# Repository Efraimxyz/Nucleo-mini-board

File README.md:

# Nucleo-mini-board
This is the design of a pcb that integrates the STM Nucleo-board along with external power capabilities.
The pcb itself has push buttons, LEDs, an OLED screen and an integrated acceleromter.

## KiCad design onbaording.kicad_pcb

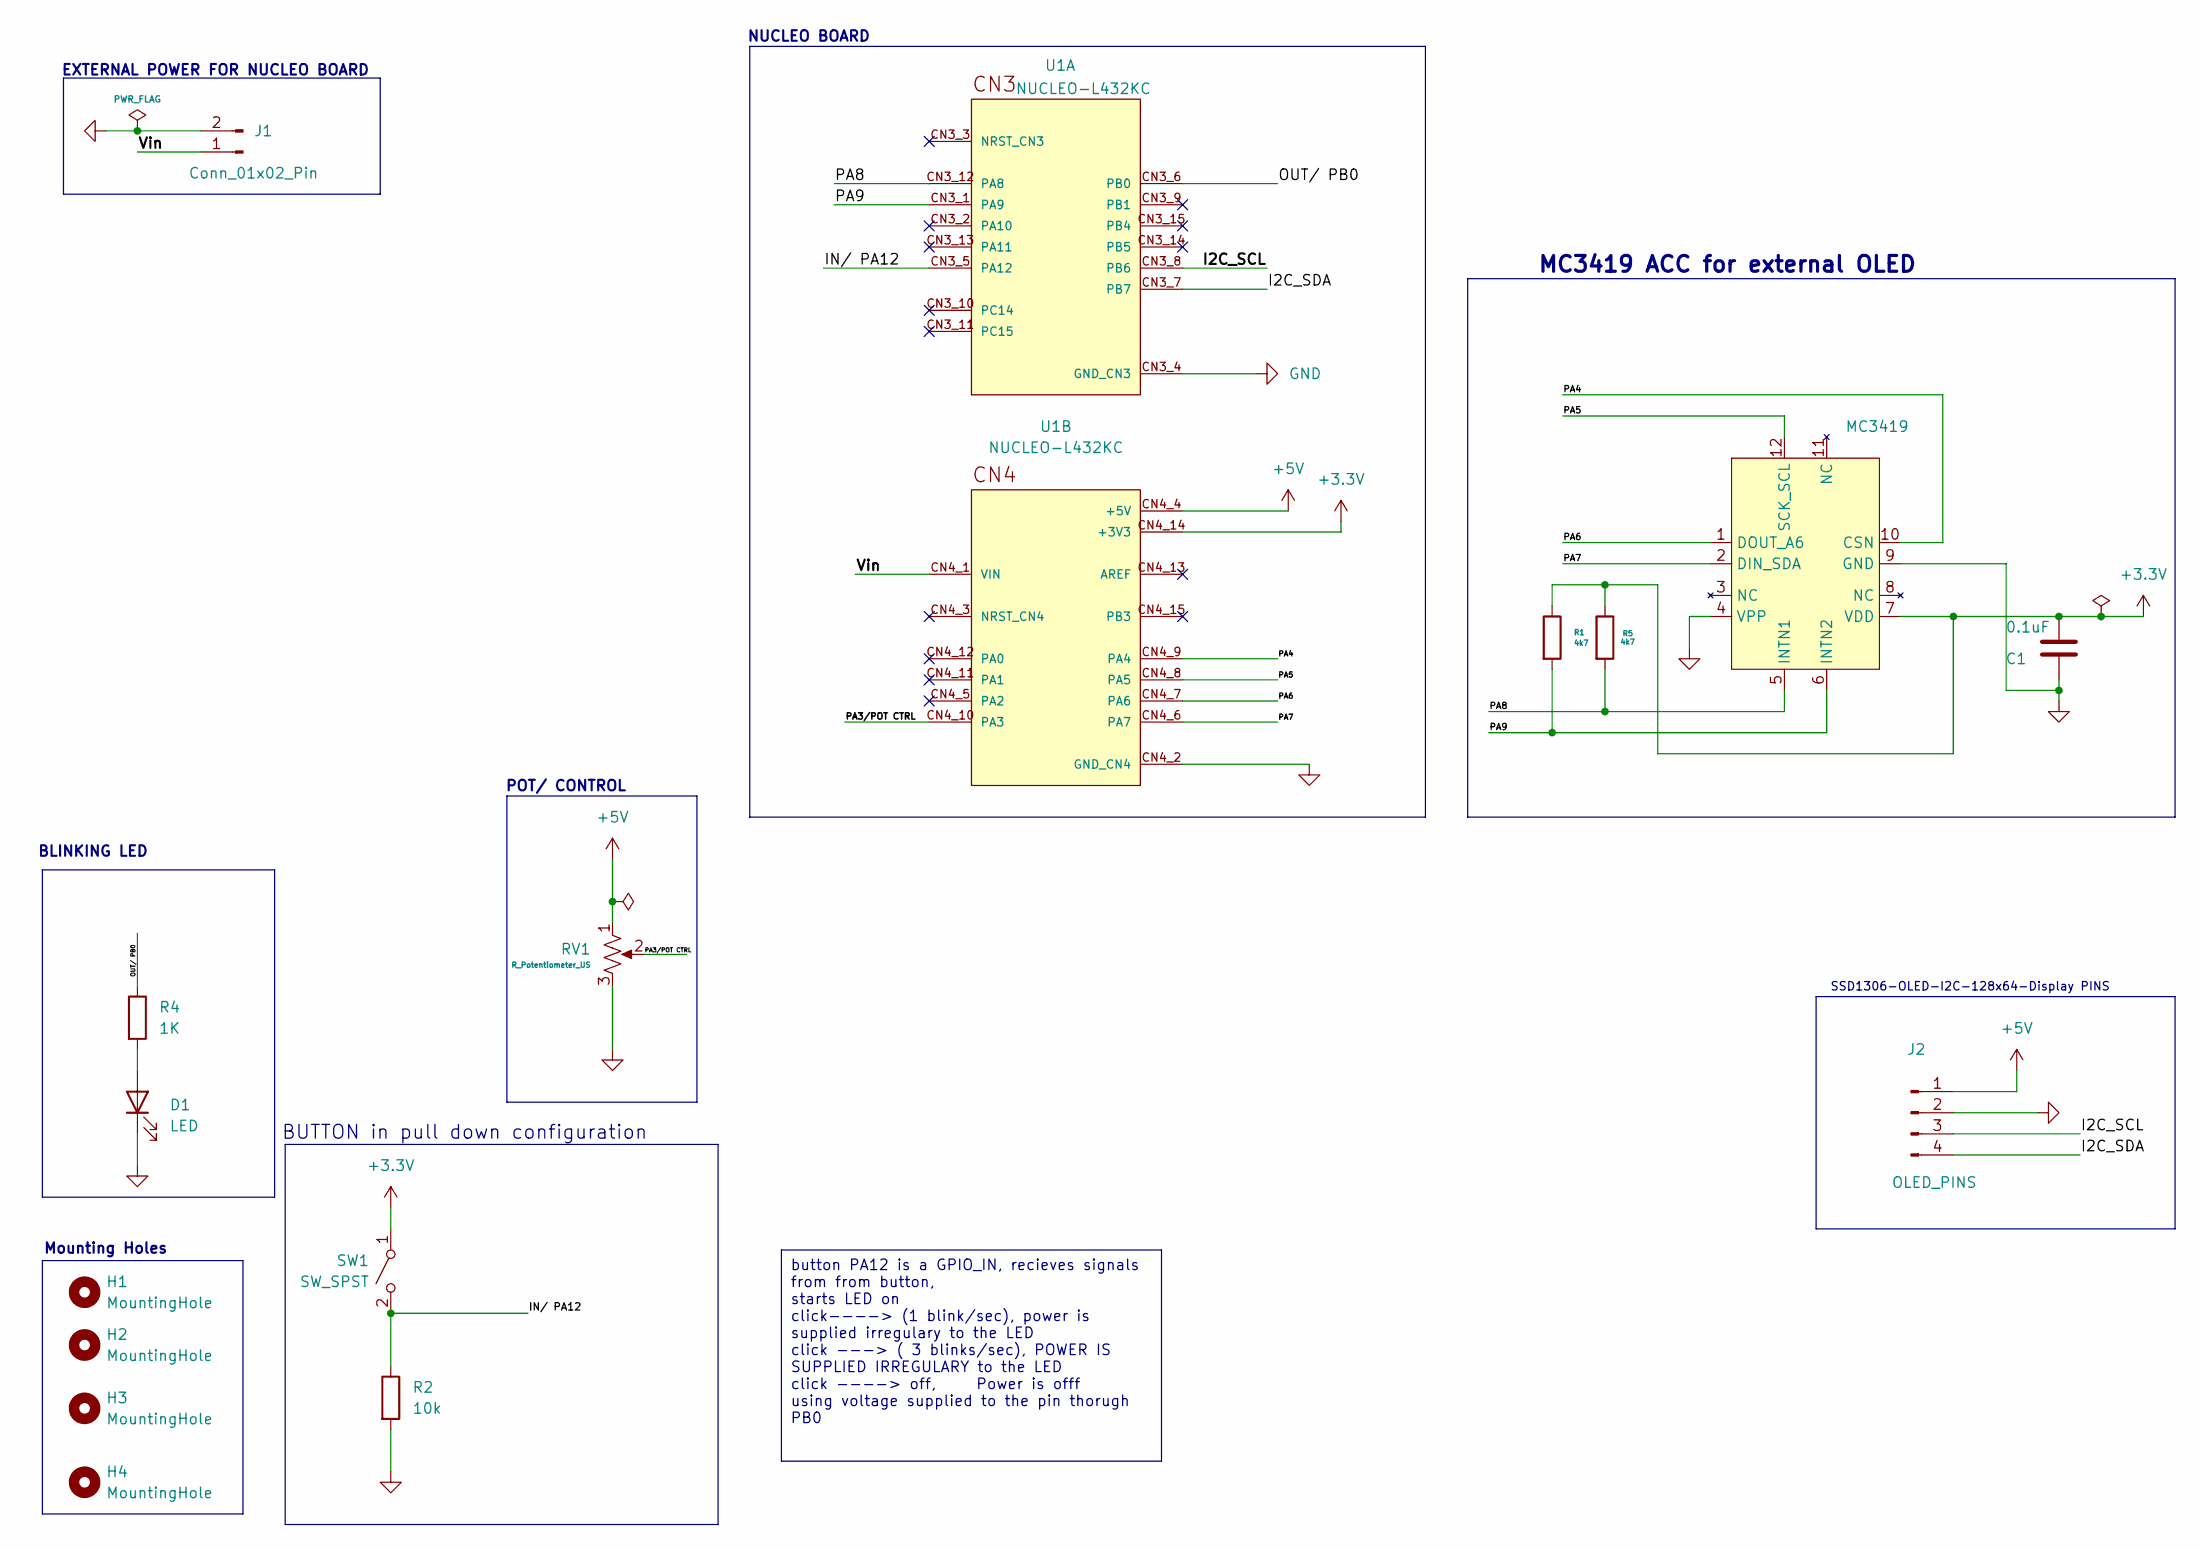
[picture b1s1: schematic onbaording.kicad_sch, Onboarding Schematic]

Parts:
C1: 0.1uF; C_0805_2012Metric
D1: LED; LED_D3.0mm
H1, H2, H3, H4: MountingHole; MountingHole_2.2mm_M2
J1: Conn_01x02_Pin; PinHeader_1x02_P2.54mm_Vertical
J2: OLED_PINS; PinHeader_1x04_P2.54mm_Vertical
MC3419: MC3479_MEM
R1, R5: 4k7; R_0402_1005Metric
R2: 10k; R_0402_1005Metric
R4: 1K; R_0402_1005Metric
RV1: R_Potentiometer_US; PTN091V05115K1B
SW1: SW_SPST; SW_SPST_B3U-1000P
U1: NUCLEO-L432KC; MODULE_NUCLEO-L432KC; PARTREV N/A

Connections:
+3.3V: C1.2, MC3419.7 (VDD), R1.1, R5.1, SW1.1 (A), U1.CN4_14 (+3V3)
+5V: J2.1, RV1.1, U1.CN4_4 (+5V)
/I2C_SCL: J2.3, U1.CN3_8 (PB6)
/I2C_SDA: J2.4, U1.CN3_7 (PB7)
/IN/ PA12: R2.1, SW1.2 (B), U1.CN3_5 (PA12)
/OUT/ PB0: R4.1, U1.CN3_6 (PB0)
/PA3/POT CTRL: RV1.2, U1.CN4_10 (PA3)
/PA4: MC3419.10 (CSN), U1.CN4_9 (PA4)
/PA5: MC3419.12 (SCK_SCL), U1.CN4_8 (PA5)
/PA6: MC3419.1 (DOUT_A6), U1.CN4_7 (PA6)
/PA7: MC3419.2 (DIN_SDA), U1.CN4_6 (PA7)
/PA8: MC3419.5 (INTN1), R5.2, U1.CN3_12 (PA8)
/PA9: MC3419.6 (INTN2), R1.2, U1.CN3_1 (PA9)
/Vin: J1.1, U1.CN4_1 (VIN)
GND: C1.1, D1.1 (K), J1.2, J2.2, MC3419.4 (VPP), MC3419.9 (GND), R2.2, RV1.3, U1.CN3_4 (GND_CN3), U1.CN4_2 (GND_CN4)
unnamed: D1.2 (A), R4.2

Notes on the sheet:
button PA12 is a GPIO_IN, recieves signals from from button, starts LED on click----> (1 blink/sec), power is supplied irregulary to the LED click ---> ( 3 blinks/sec), POWER IS SUPPLIED IRREGULARY to the LED click ----> off, Power is offf using voltage supplied to the pin thorugh PB0
EXTERNAL POWER FOR NUCLEO BOARD
BLINKING LED
Mounting Holes
SSD1306-OLED-I2C-128x64-Display PINS
MC3419 ACC for external OLED
POT/ CONTROL
NUCLEO BOARD
BUTTON in pull down configuration

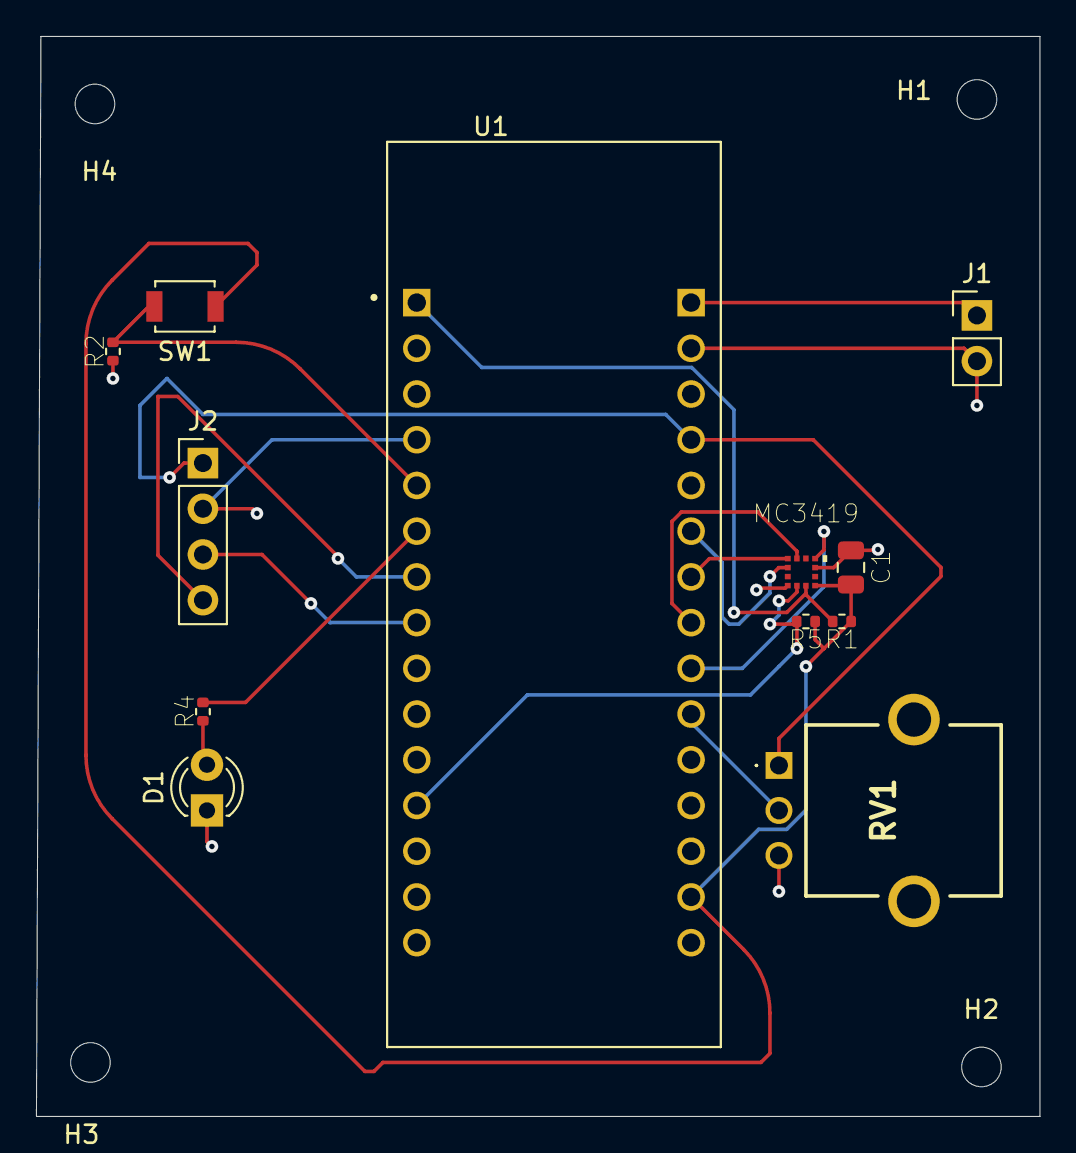
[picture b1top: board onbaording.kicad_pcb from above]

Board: 2 copper layers, 55.8 x 60.0 mm, 16 parts (0 on the bottom side), 16 nets.

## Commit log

2025-10-29 Updated layout
